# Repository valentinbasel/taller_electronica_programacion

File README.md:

# taller_electronica_programacion

taller de programación y diseño de circuitos usando software libre y hardware del proyecto PINGUINO (18F2550)

## introducción

En la actualidad, los sistemas digitales son cada ves mas transversales a nuestra vida cotidiana, sin embargo el nivel de desconocimiento que se tiene sobre los procesos de diseño, fabricación y programación de los dispositivos electrónicos digitales es enorme, casi se podría decir que estamos ante un oscurantismo tecnológico, en el marco de el segundo cercamiento de los bienes comunes (Boyle, 2003). 

Abordar un proyecto de robótica como Recurso Educativo Abierto (REA/OER), implica una serie de desarrollos conceptuales y teóricos que van a más allá del diseño y desarrollo técnico de hardware y software. El uso de REA/OER (Montoya y Aguilar, 2012) implica un compromiso político-epistemológico con respecto al uso de la tecnología, esto es, la apropiación de términos conceptuales como ”software libre”, ”soberanía tecnológica” y cultura libre.

## Taller

Este repositorio esta diseñado para ir desarrollando un taller de electrónica básica, donde abordaremos el diseño de un PCB (Printed circuit board)de simple faz, para la construcción de un circuito basado en el micro controlador 18F2550.

Luego pasaremos a programar el micro controlador mediante las librerías del proyecto PINGUINO-BOARD (usando el software ICARO), viendo formas de programarlo en lenguaje de bloques (icaro-bloques), lenguaje C y controlar la placa (como un datalogger) mediante PYTHON.

## Repositorio 

En este repositorio, vamos a ir almacenando toda la información pertinente para el desarrollo del curso, desde lista de materiales, dinamica de trabajo, archivos KICAD y presentaciones del curso.

## Cronograma

El taller esta dividido en 2 momentos, cada uno de 2 horas (aunque se pueden estirar en función de las necesidades).

### Primer momento

- presentación del taller y los objetivos (diapositiva). 
- Preparación de las notebook que se usaran en el taller (levantar live usb de FEDORA).
- introducción al diseño de pcbs con KICAD.
- impresión y transferencia del PCB para luego atacarlo con cloruro férrico.
- soldadura de los componentes electrónicos y prueba del bootloader V4 de pinguino.

### Segundo momento

- Abordaremos los aspectos del uso de software para cargar un firmware en los micro controladores (usando icaro-bloques)
- comunicación USB-CDC mediante el pic y la PC.
- un taller de programación en PYTHON
- una introducción a los sistemas de visión artificial, usando las librerias open-cv.

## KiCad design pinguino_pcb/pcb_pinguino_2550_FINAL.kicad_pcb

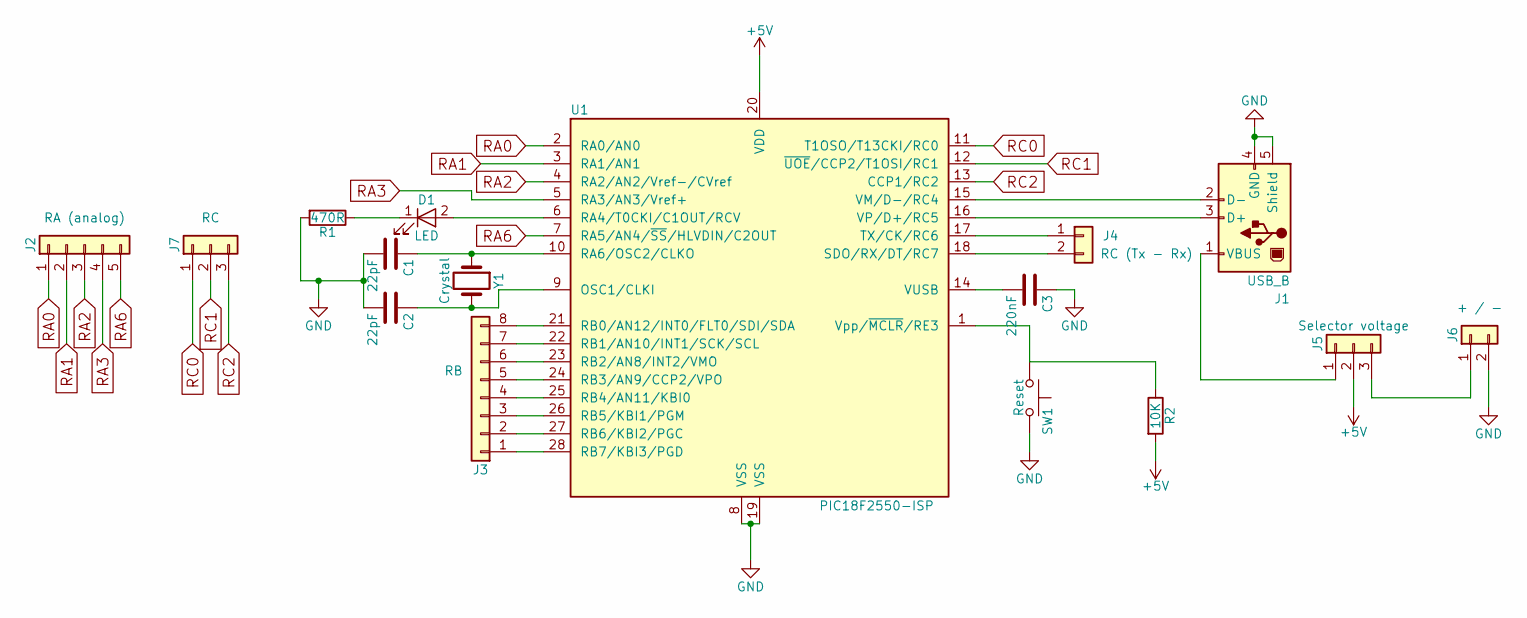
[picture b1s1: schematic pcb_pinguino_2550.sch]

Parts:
C1, C2: 22pF; C_Disc_D5.0mm_W2.5mm_P5.00mm
C3: 220nF; C_Disc_D5.0mm_W2.5mm_P5.00mm
D1: LED; LED_D5.0mm
J1: USB_B
J2: RA (analog); Pin_Header_Straight_1x05_Pitch2.54mm
J3: RB; Pin_Header_Straight_1x08_Pitch2.54mm
J4: RC (Tx - Rx); Pin_Header_Straight_1x02_Pitch2.54mm
J5: Selector voltage; Pin_Header_Straight_1x03_Pitch2.54mm
J6: + / -; Pin_Header_Straight_1x02_Pitch2.54mm
J7: RC; Pin_Header_Straight_1x03_Pitch2.54mm
R1: 470R; R_Axial_DIN0207_L6.3mm_D2.5mm_P10.16mm_Horizontal
R2: 10K; R_Axial_DIN0207_L6.3mm_D2.5mm_P10.16mm_Horizontal
SW1: Reset; SW_PUSH_6mm_h5mm
U1: PIC18F2550-ISP; DIP-28_W15.24mm_LongPads
Y1: Crystal; Crystal_HC49-U_Vertical

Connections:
+5V: J5.2, R2.2, U1.20 (VDD)
GND: C1.2, C2.2, C3.1, J1.4 (GND), J1.5 (Shield), J6.2, R1.2, SW1.2, U1.8 (VSS), U1.19 (VSS)
unnamed: C1.1, U1.10 (RA6/OSC2/CLKO), Y1.1
unnamed: C2.1, U1.9 (OSC1/CLKI), Y1.2
unnamed: C3.2, U1.14 (VUSB)
unnamed: D1.1 (K), R1.1
unnamed: D1.2 (A), U1.6 (RA4/T0CKI/C1OUT/RCV)
unnamed: J1.1 (VBUS), J5.1
unnamed: J1.2 (D-), U1.15 (VM/D-/RC4)
unnamed: J1.3 (D+), U1.16 (VP/D+/RC5)
unnamed: J3.1, U1.28 (RB7/KBI3/PGD)
unnamed: J3.2, U1.27 (RB6/KBI2/PGC)
unnamed: J3.3, U1.26 (RB5/KBI1/PGM)
unnamed: J3.4, U1.25 (RB4/AN11/KBI0)
unnamed: J3.5, U1.24 (RB3/AN9/CCP2/VPO)
unnamed: J3.6, U1.23 (RB2/AN8/INT2/VMO)
unnamed: J3.7, U1.22 (RB1/AN10/INT1/SCK/SCL)
unnamed: J3.8, U1.21 (RB0/AN12/INT0/FLT0/SDI/SDA)
unnamed: J4.1, U1.17 (TX/CK/RC6)
unnamed: J4.2, U1.18 (SDO/RX/DT/RC7)
unnamed: J5.3, J6.1
unnamed: R2.1, SW1.1, U1.1 (Vpp/~MCLR~/RE3)
RA0: J2.1, U1.2 (RA0/AN0)
RA1: J2.2, U1.3 (RA1/AN1)
RA2: J2.3, U1.4 (RA2/AN2/Vref-/CVref)
RA3: J2.4, U1.5 (RA3/AN3/Vref+)
RA6: J2.5, U1.7 (RA5/AN4/~SS~/HLVDIN/C2OUT)
RC0: J7.1, U1.11 (T1OSO/T13CKI/RC0)
RC1: J7.2, U1.12 (~UOE~/CCP2/T1OSI/RC1)
RC2: J7.3, U1.13 (CCP1/RC2)

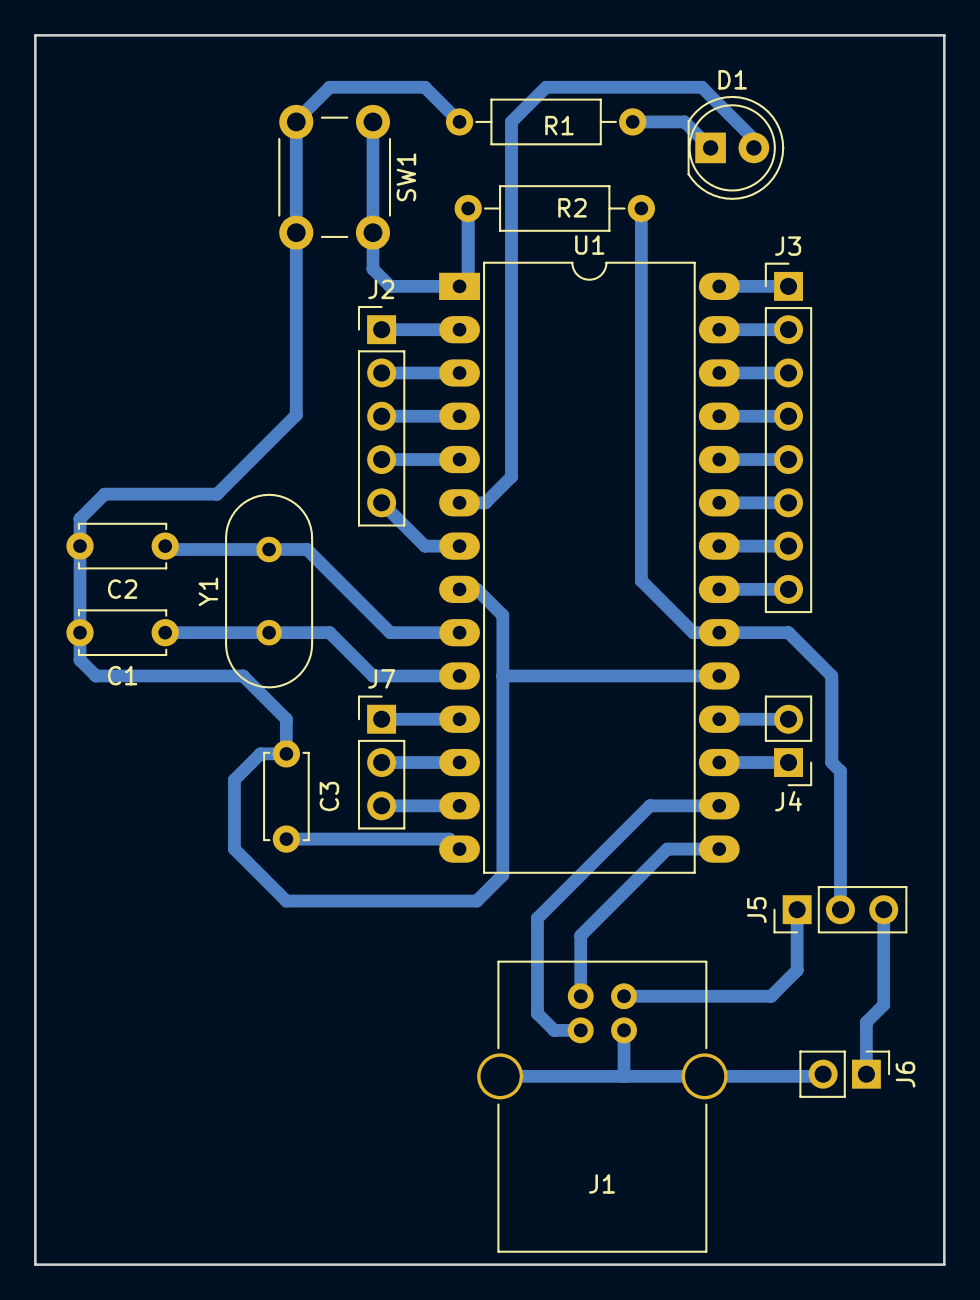
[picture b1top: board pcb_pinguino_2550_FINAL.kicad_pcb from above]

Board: 2 copper layers, 53.3 x 72.1 mm, 16 parts (0 on the bottom side), 30 nets.

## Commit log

2018-03-11 agrego el listado de herramientas, materiales y los archivs para kicad
2018-03-11 cambios menores
